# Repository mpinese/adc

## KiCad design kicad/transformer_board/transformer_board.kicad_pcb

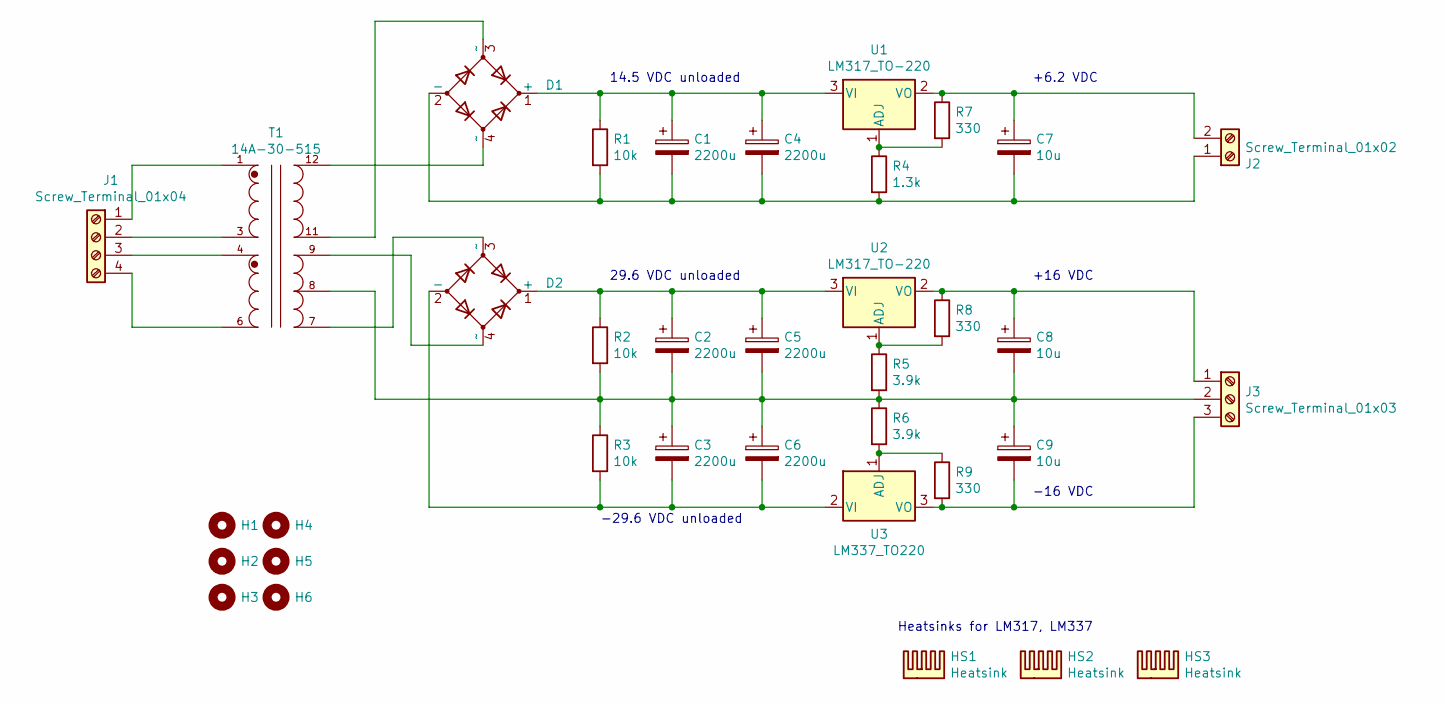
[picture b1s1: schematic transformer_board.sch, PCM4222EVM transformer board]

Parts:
C1, C4: 2200u; CP_Radial_D10.0mm_P5.00mm; DigiKey 565-3869-ND
C2, C3, C5, C6: 2200u; CP_Radial_D12.5mm_P5.00mm; DigiKey 565-3923-ND
C7, C8, C9: 10u; CP_Radial_D5.0mm_P2.00mm; DigiKey 732-9501-1-ND
D1, D2: D_Bridge_+-AA; Diode_Bridge_DIP-4_W7.62mm_P5.08mm; DigiKey DF02MDI-ND
H1, H2, H3, H4, H5, H6: MountingHole; MountingHole_3.2mm_M3
HS1, HS2, HS3: Heatsink; AAVID_504102B00000G; DigiKey HS104-1-ND
J1: Screw_Terminal_01x04; TerminalBlock_Phoenix_PT-1,5-4-5.0-H_1x04_P5.00mm_Horizontal; DigiKey 277-1579-ND
J2: Screw_Terminal_01x02; TerminalBlock_Phoenix_PT-1,5-2-5.0-H_1x02_P5.00mm_Horizontal; DigiKey 277-1667-ND
J3: Screw_Terminal_01x03; TerminalBlock_Phoenix_PT-1,5-3-5.0-H_1x03_P5.00mm_Horizontal; DigiKey 277-1578-ND
R1, R2, R3: 10k; R_Axial_DIN0207_L6.3mm_D2.5mm_P7.62mm_Horizontal; DigiKey PPC10.0KYCT-ND
R4: 1.3k; R_Axial_DIN0207_L6.3mm_D2.5mm_P7.62mm_Horizontal; DigiKey PPC1.30KYCT-ND
R5, R6: 3.9k; R_Axial_DIN0207_L6.3mm_D2.5mm_P7.62mm_Horizontal; DigiKey 56-SFR2500003901FR500CT-ND
R7, R9: 330; R_Axial_DIN0207_L6.3mm_D2.5mm_P7.62mm_Horizontal; DigiKey BC4366CT-ND
R8: 330; R_Axial_DIN0207_L6.3mm_D2.5mm_P7.62mm_Horizontal; DigiKey 56-SFR25H0003300FR500CT-ND
T1: 14A-30-515; XFMR_14A-30-515; DigiKey 595-1828-ND
U1, U2: LM317_TO-220; TO-220-3_Horizontal_TabDown; DigiKey 497-19621-ND
U3: LM337_TO220; TO-220-3_Horizontal_TabDown; DigiKey LM337TGOS-ND

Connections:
unnamed: C1.1, C4.1, D1.1 (+), R1.1, U1.3 (VI)
unnamed: C1.2, C4.2, C7.2, D1.2 (-), J2.1, R1.2, R4.2
unnamed: C2.1, C5.1, D2.1 (+), R2.1, U2.3 (VI)
unnamed: C2.2, C3.1, C5.2, C6.1, C8.2, C9.1, J3.2, R2.2, R3.1, R5.2, R6.1, T1.8
unnamed: C3.2, C6.2, D2.2 (-), R3.2, U3.2 (VI)
unnamed: C7.1, J2.2, R7.1, U1.2 (VO)
unnamed: C8.1, J3.1, R8.1, U2.2 (VO)
unnamed: C9.2, J3.3, R9.2, U3.3 (VO)
unnamed: D1.3 (~~), T1.11
unnamed: D1.4 (~~), T1.12
unnamed: D2.3 (~~), T1.7
unnamed: D2.4 (~~), T1.9
unnamed: J1.1, T1.1
unnamed: J1.2, T1.3
unnamed: J1.3, T1.4
unnamed: J1.4, T1.6
unnamed: R4.1, R7.2, U1.1 (ADJ)
unnamed: R5.1, R8.2, U2.1 (ADJ)
unnamed: R6.2, R9.1, U3.1 (ADJ)

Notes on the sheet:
14.5 VDC unloaded
29.6 VDC unloaded
-29.6 VDC unloaded
+16 VDC
-16 VDC
Heatsinks for LM317, LM337
+6.2 VDC

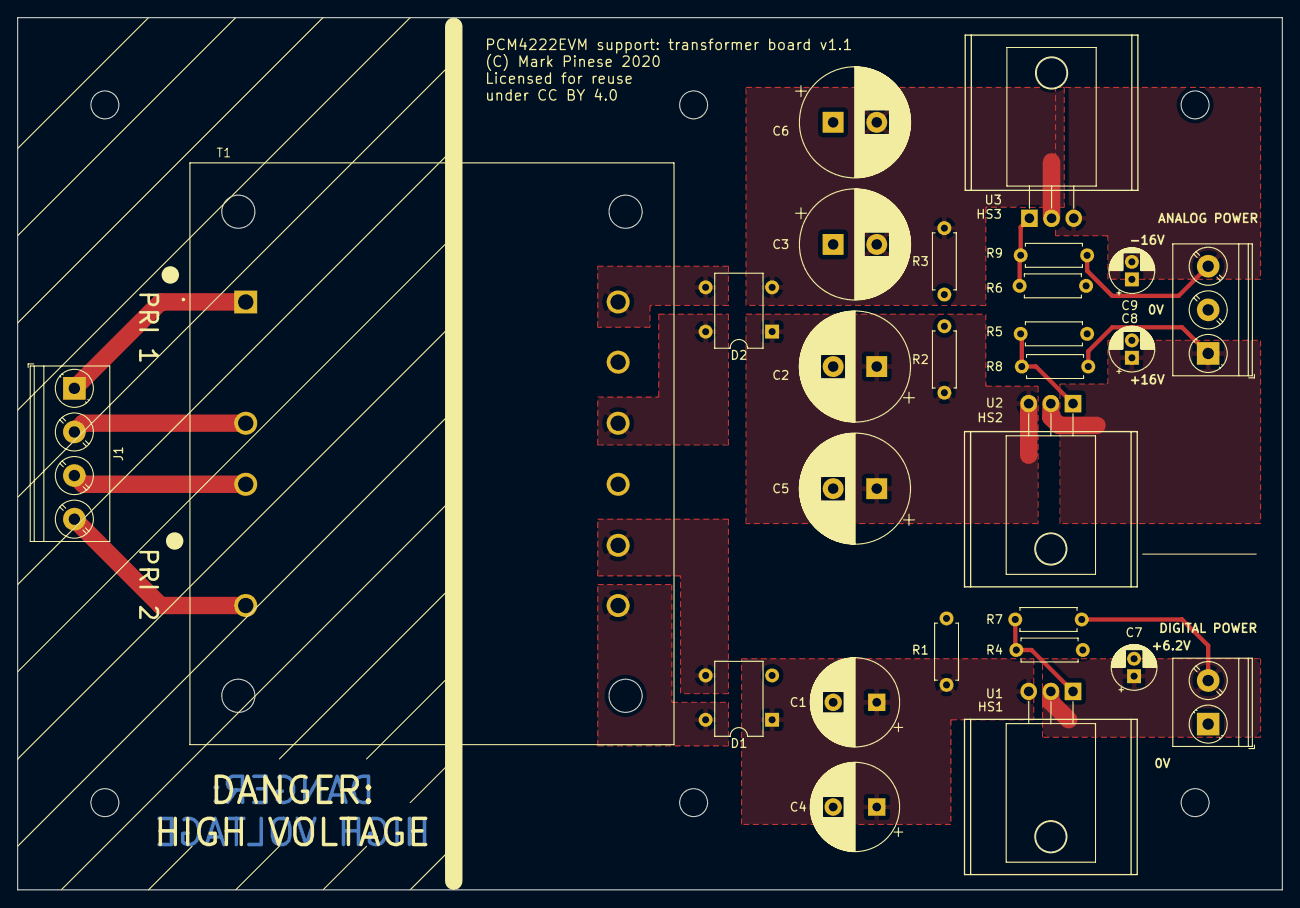
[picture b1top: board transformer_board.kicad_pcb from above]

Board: 2 copper layers, 145.0 x 100.0 mm, 36 parts (0 on the bottom side), 19 nets.

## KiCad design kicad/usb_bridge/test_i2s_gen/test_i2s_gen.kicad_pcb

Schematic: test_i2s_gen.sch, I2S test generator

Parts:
C1: 10u; C_0805_2012Metric; DigiKey 1276-1764-1-ND
C2, C5: 27p; C_0603_1608Metric; DigiKey 311-3929-1-ND
C3: 470n; C_0603_1608Metric; DigiKey 311-1078-1-ND
C4, C6, C7, C8, C9: 100n; C_0603_1608Metric; DigiKey 399-1099-1-ND
H1, H2, H3, H4: MountingHole; MountingHole_2.2mm_M2
J1: Conn_01x02_Male; PinHeader_1x02_P2.54mm_Vertical
J2: Conn_01x04_Male; PinHeader_1x04_P2.54mm_Vertical
R1: 14k; R_0603_1608Metric; DigiKey CR0603-FX-1402ELFCT-ND
R2: 1M; R_0603_1608Metric; DigiKey CR0603-JW-105ELFCT-ND
R3: 21k; R_0603_1608Metric; DigiKey CR0603-FX-2102ELFCT-ND
R4: 4.7k; R_0603_1608Metric; DigiKey CR0603-JW-472ELFCT-ND
S1: 1825910-6; Switch_Tactile_THT_6x6mm; DigiKey 450-1650-ND
U1: SN74AC14DR; SOIC-14_3.9x8.7mm_P1.27mm; DigiKey 296-4300-1-ND
U2: 74AHC86; SOIC-14_3.9x8.7mm_P1.27mm; DigiKey 296-4625-5-ND
U3: 74HC4020; SOIC-16_3.9x9.9mm_P1.27mm; DigiKey MC74HC4020ADR2GOSCT-ND
U4, U5: 74AHC595; SOIC-16_3.9x9.9mm_P1.27mm; DigiKey 1727-5926-1-ND
Y1: Crystal; Crystal_SMD_HC49-SD; DigiKey XC2780CT-ND

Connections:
+3V3: C1.1, C4.1, C6.1, C7.1, C8.1, C9.1, J1.1, R1.2, U1.14, U2.13, U2.14, U3.16, U4.16, U5.16
/BCK: J2.3, U1.8, U3.10, U4.11, U4.12, U5.11, U5.12
/DATA: J2.2, U1.12
/LRCK: J2.4, U1.6
/Reset: U1.1, U1.4, U3.11
/~Reset: U1.2, U4.10, U5.10
GNDD: C1.2, C2.2, C3.2, C4.2, C5.2, C6.2, C7.2, C8.2, C9.2, J1.2, J2.1, R3.1, S1.3, S1.4, U1.7, U2.7, U3.8, U4.8, U4.13, U5.8, U5.13
unnamed: C2.1, R2.2, U1.11, Y1.1
unnamed: C3.1, R1.1, R3.2, S1.1, S1.2, U1.3
unnamed: C5.1, R4.1, Y1.2
unnamed: R2.1, R4.2, U1.9, U1.10
unnamed: U1.5, U3.4
unnamed: U1.13, U2.2, U5.7
unnamed: U2.1, U5.6
unnamed: U2.3, U2.5
unnamed: U2.4, U5.4
unnamed: U2.9, U4.3
unnamed: U2.6, U2.10
unnamed: U2.11, U4.14
unnamed: U2.8, U2.12
unnamed: U4.9, U5.14

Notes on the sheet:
Very basic circuit to test the I2S to USB bridge. Generates left-justified test audio data at 96 kHz 32 bit stereo. This is not strictly I2S format but can be interpreted as such. Simple LFSR to produce the bitstream, so does not test all codes, and would NOT be a good white noise source. 96 kHz st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
Power-on reset circuit. Delay 10 ms.
Vcc: 2.0 to 5.5 V

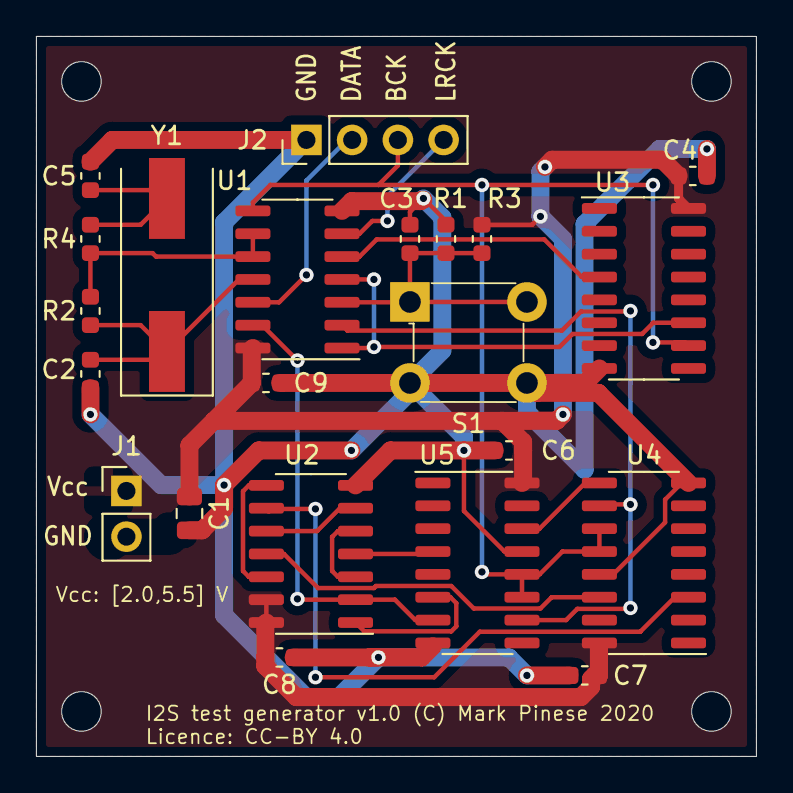
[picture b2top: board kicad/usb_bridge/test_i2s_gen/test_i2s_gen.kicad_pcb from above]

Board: 2 copper layers, 40.0 x 40.0 mm, 26 parts (0 on the bottom side), 21 nets.

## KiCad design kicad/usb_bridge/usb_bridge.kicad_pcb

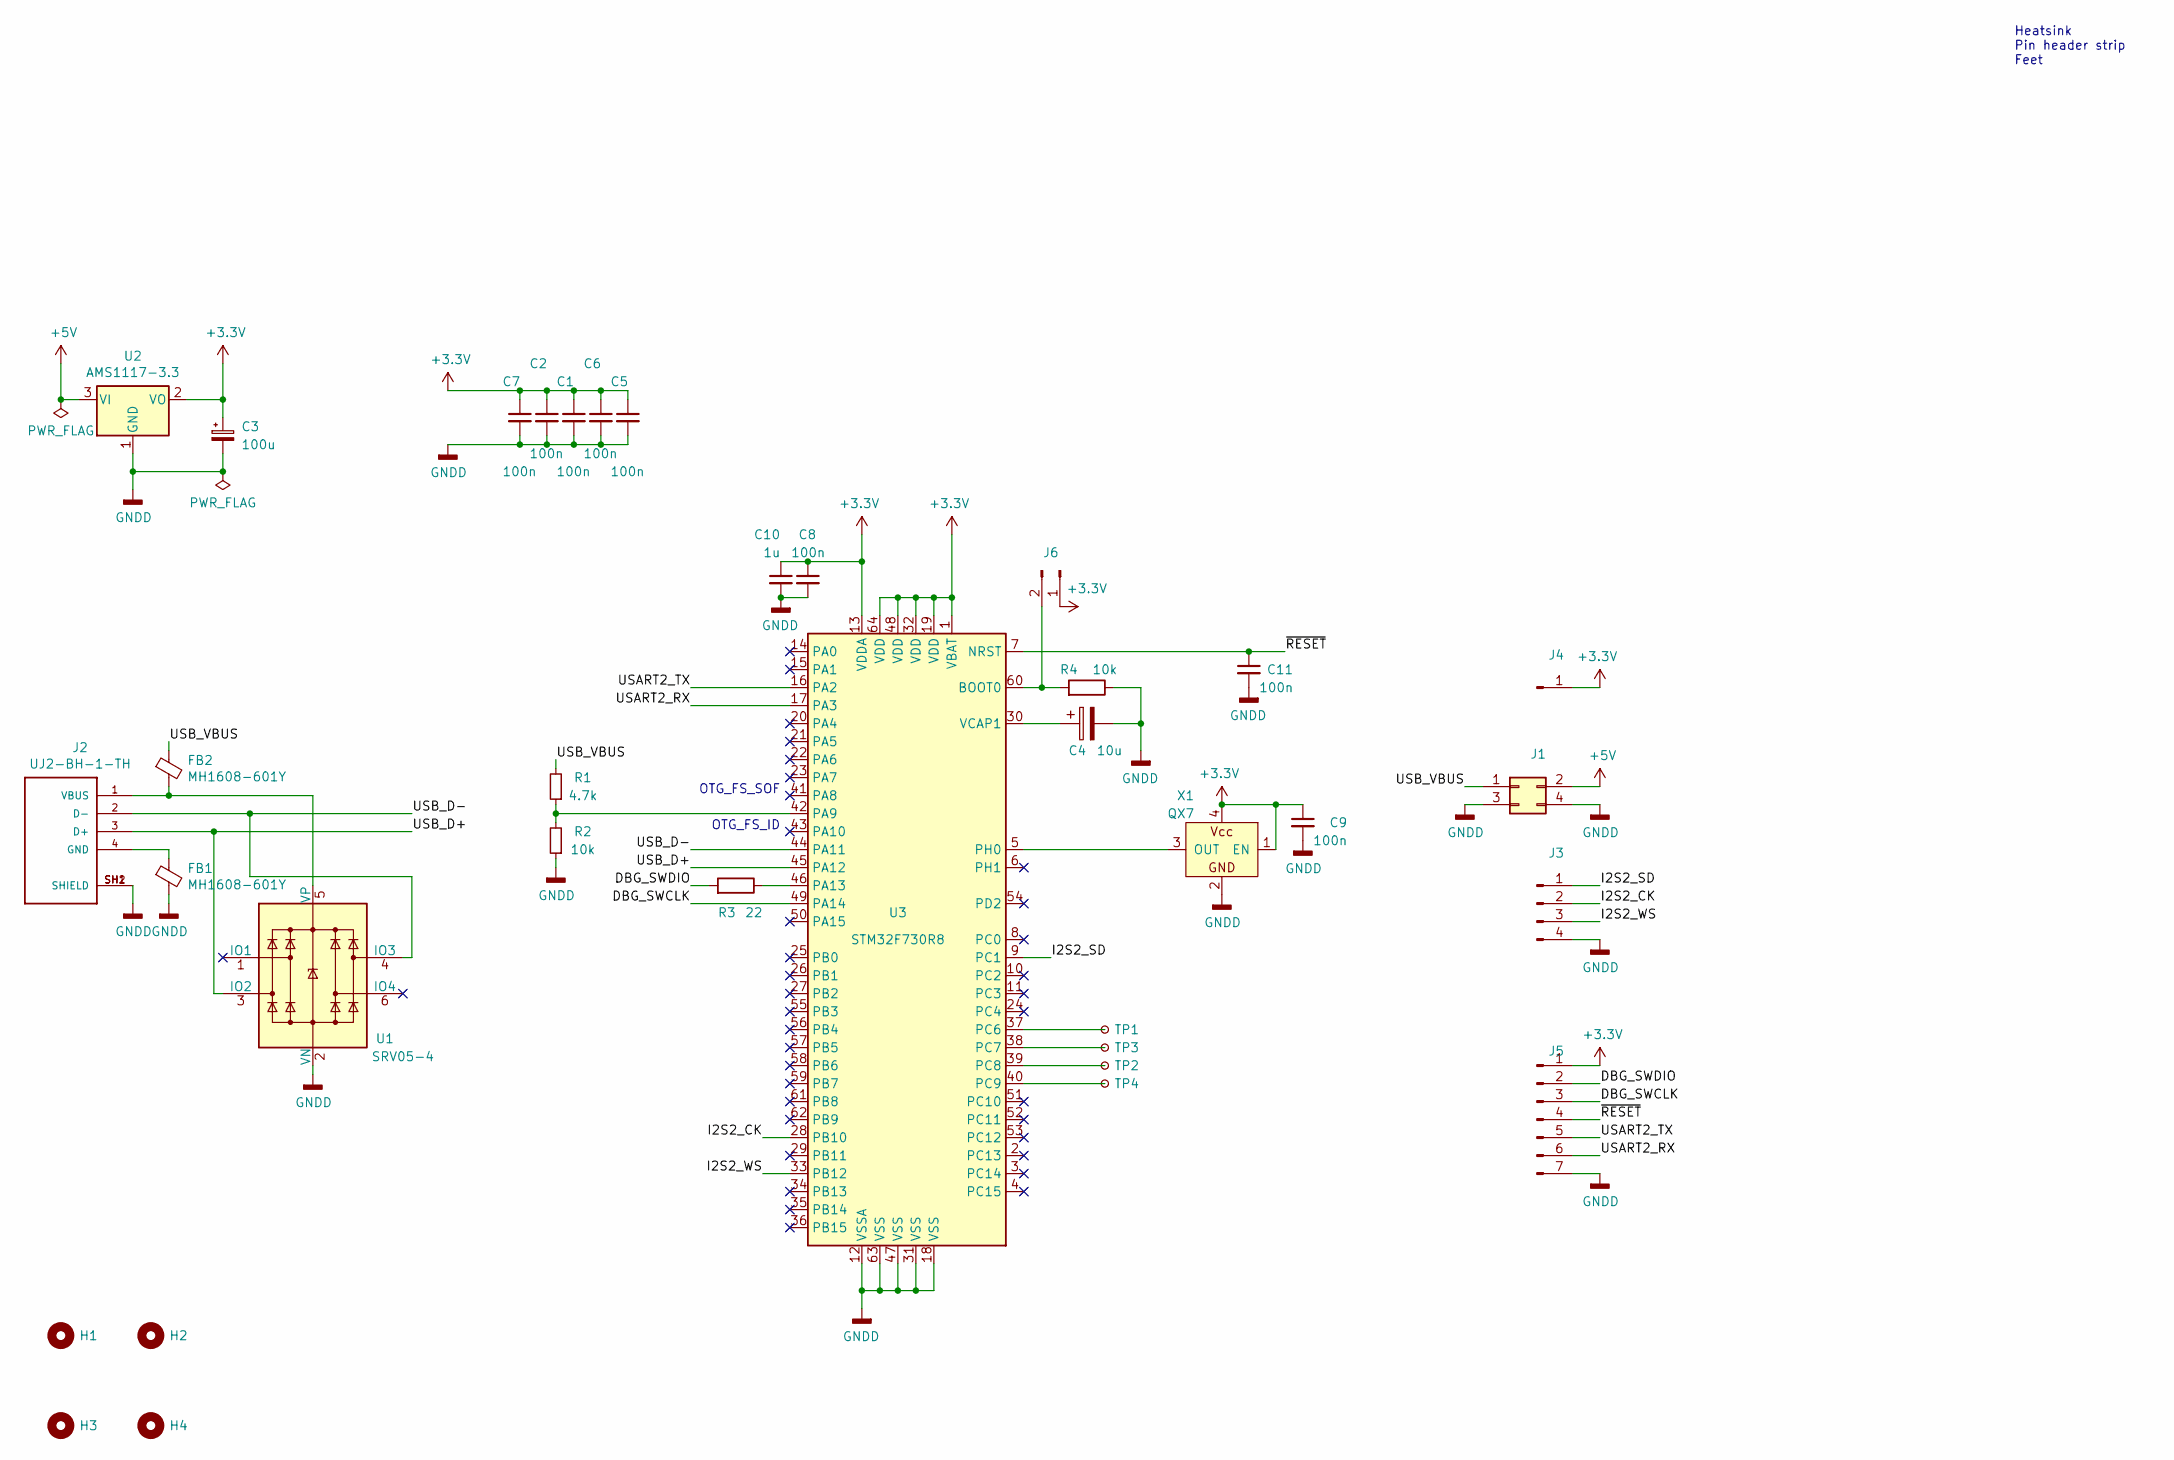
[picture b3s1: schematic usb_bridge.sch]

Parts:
C1, C2, C5, C6, C7, C8, C9, C11: 100n; C_0402_1005Metric; LCSC C1525
C3: 100u; CP_EIA-3528-21_Kemet-B; LCSC C16133
C4: 10u; CP_EIA-2012-15_AVX-P_Pad1.30x1.05mm_HandSolder; DigiKey 718-2064-1-ND
C10: 1u; C_0402_1005Metric; LCSC C52923
FB1, FB2: MH1608-601Y; L_0603_1608Metric; DigiKey MH1608-601YCT-ND
H1, H2, H3, H4: MountingHole; MountingHole_3.2mm_M3
J1: Conn_01x02_Male; PinHeader_2x02_P2.54mm_Vertical
J2: UJ2-BH-1-TH; CUI_UJ2-BH-1-TH; DigiKey 102-3999-ND
J3: Conn_01x04_Male; PinHeader_1x04_P2.54mm_Vertical
J4: Conn_01x01_Male; PinHeader_1x01_P2.54mm_Vertical
J5: Conn_01x07_Male; PinHeader_1x07_P2.54mm_Vertical
J6: Conn_01x02_Male; PinHeader_1x02_P2.54mm_Vertical
R1: 4.7k; R_0402_1005Metric; LCSC C25900
R2, R4: 10k; R_0402_1005Metric; LCSC C25744
R3: 22; R_0402_1005Metric; LCSC C25092
TP1, TP2, TP3, TP4: TestPoint_Small; TestPoint_Pad_D1.0mm
U1: SRV05-4; SOT-23-6; LCSC C85364
U2: AMS1117-3.3; SOT-223-3_TabPin2; LCSC C6186
U3: STM32F730R8; LQFP-64_10x10mm_P0.5mm; DigiKey 497-18103-ND
X1: QX7; QTX333

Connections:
+3V3: C1.1, C2.1, C3.1, C5.1, C6.1, C7.1, C8.1, C9.1, C10.1, J4.1, J5.1, J6.1, U2.2 (VO), U3.1 (VBAT), U3.13 (VDDA), U3.19 (VDD), U3.32 (VDD), U3.48 (VDD), U3.64 (VDD), X1.1 (EN), X1.4
+5V: J1.2, U2.3 (VI)
/DBG_SWCLK: J5.3, U3.49 (PA14)
/DBG_SWDIO: J5.2, R3.2
/I2S2_CK: J3.2, U3.28 (PB10)
/I2S2_SD: J3.1, U3.9 (PC1)
/I2S2_WS: J3.3, U3.33 (PB12)
/USART2_RX: J5.6, U3.17 (PA3)
/USART2_TX: J5.5, U3.16 (PA2)
/USB_D+: J2.3 (D+), U1.3 (IO2), U3.45 (PA12)
/USB_D-: J2.2 (D-), U1.4 (IO3), U3.44 (PA11)
/USB_VBUS: FB2.1, J1.1, R1.2
/~RESET: C11.1, J5.4, U3.7 (NRST)
GNDD: C1.2, C2.2, C3.2, C4.2, C5.2, C6.2, C7.2, C8.2, C9.2, C10.2, C11.2, FB1.2, J1.3, J1.4, J2.SH1 (SHIELD), J2.SH2 (SHIELD), J3.4, J5.7, R2.1, R4.1, U1.2 (VN), U2.1 (GND), U3.12 (VSSA), U3.18 (VSS), U3.31 (VSS), U3.47 (VSS), U3.63 (VSS), X1.2
unnamed: C4.1, U3.30 (VCAP1)
unnamed: FB1.1, J2.4 (GND)
unnamed: FB2.2, J2.1 (VBUS), U1.5 (VP)
unnamed: J6.2, R4.2, U3.60 (BOOT0)
unnamed: R1.1, R2.2, U3.42 (PA9)
unnamed: R3.1, U3.46 (PA13)
unnamed: TP1.1, U3.37 (PC6)
unnamed: TP2.1, U3.39 (PC8)
unnamed: TP3.1, U3.38 (PC7)
unnamed: TP4.1, U3.40 (PC9)
unnamed: U3.5 (PH0), X1.3 (OUT)

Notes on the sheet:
Heatsink Pin header strip Feet
OTG_FS_SOF
OTG_FS_ID

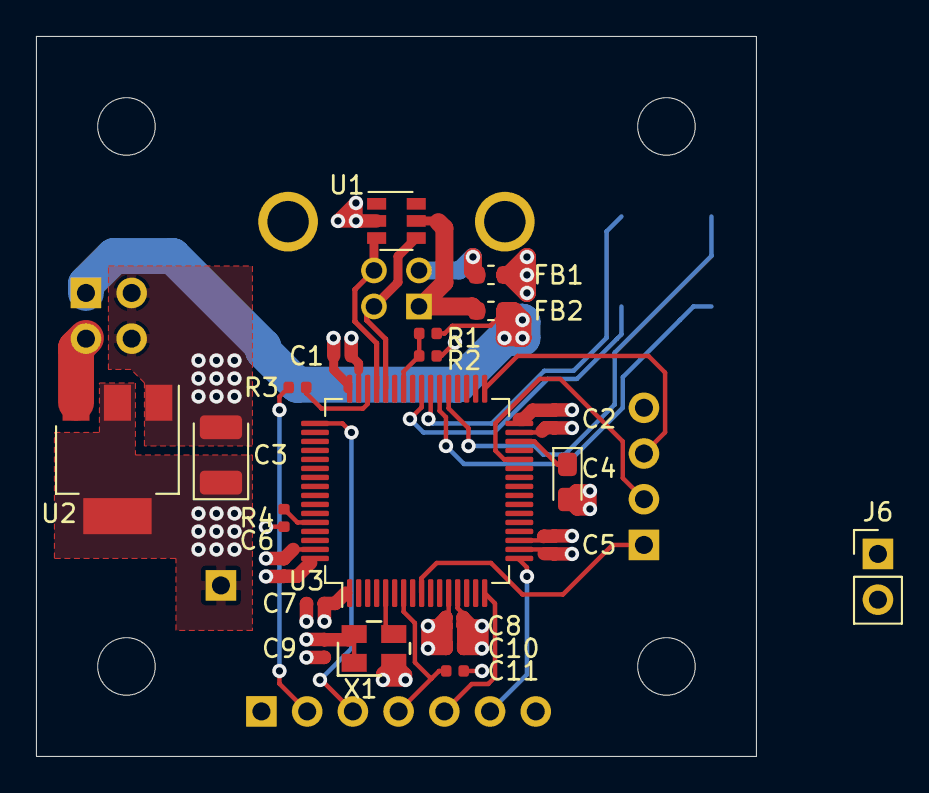
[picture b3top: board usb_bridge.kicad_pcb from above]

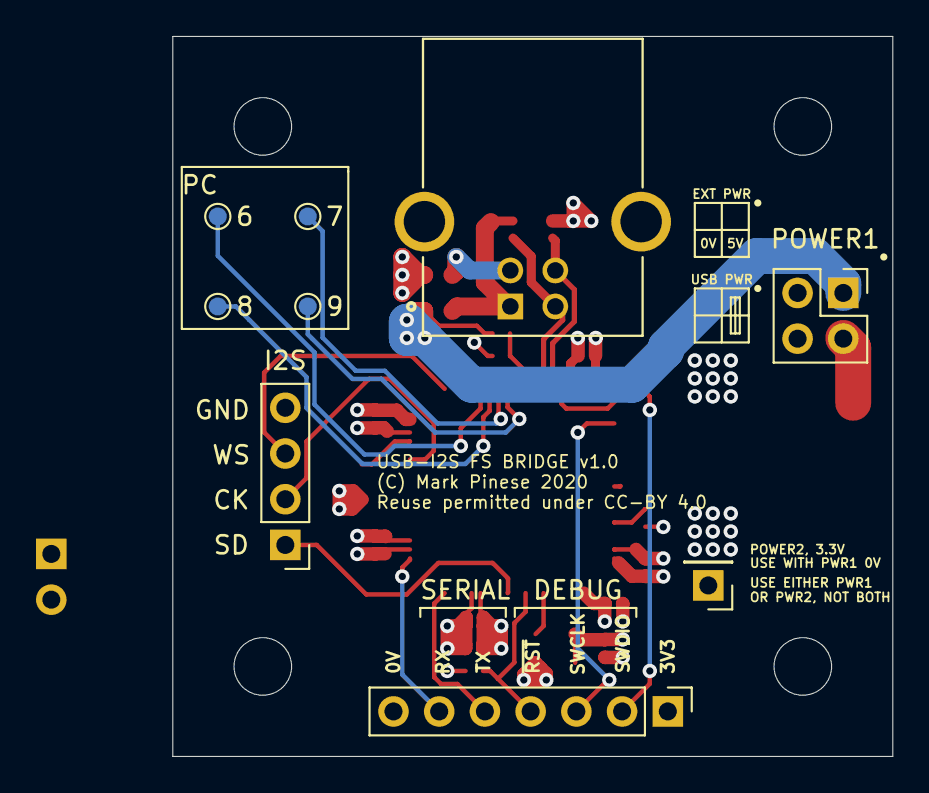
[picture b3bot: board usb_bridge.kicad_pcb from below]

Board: 4 copper layers, 40.0 x 40.0 mm, 35 parts (9 on the bottom side), 25 nets.

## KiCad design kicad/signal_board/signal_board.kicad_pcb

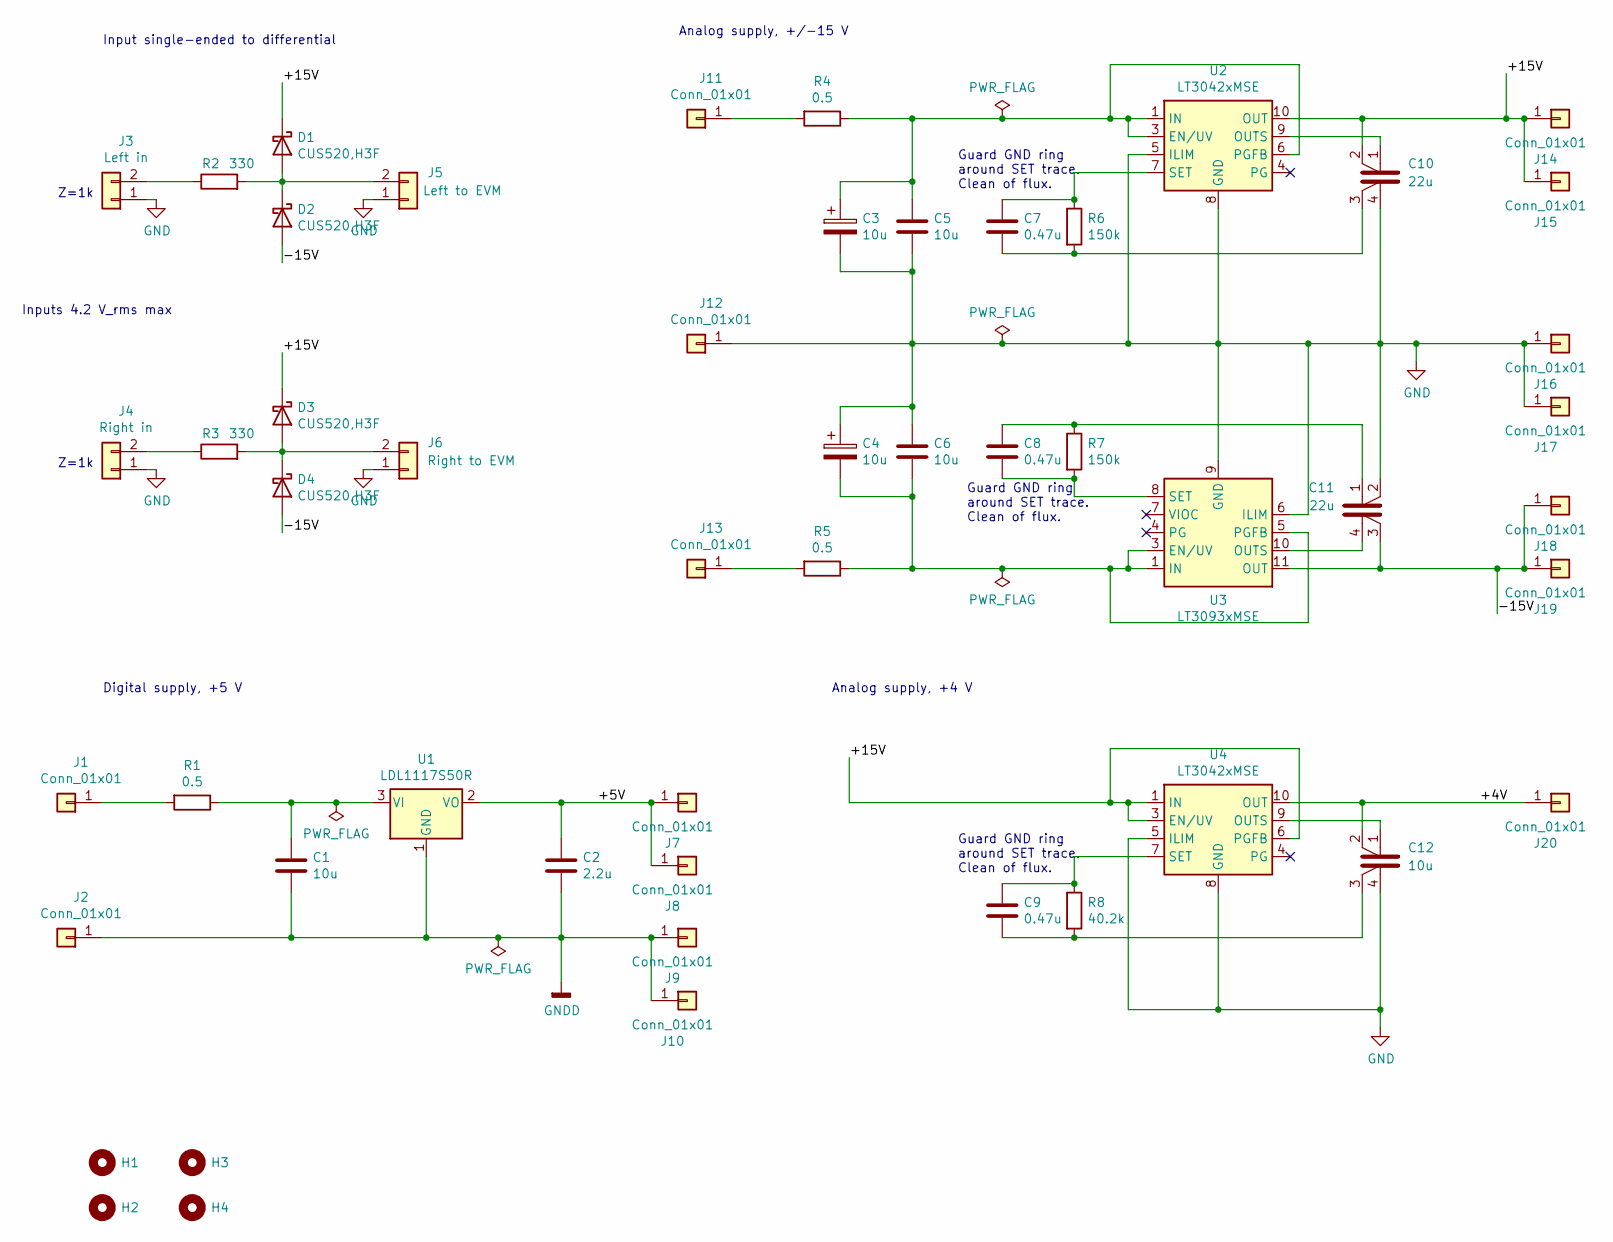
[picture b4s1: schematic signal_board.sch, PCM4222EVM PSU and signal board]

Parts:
C1: 10u; C_1206_3216Metric; DigiKey 1276-6767-1-ND
C2: 2.2u; C_0805_2012Metric; DigiKey 1276-6655-1-ND
C3, C4: 10u; CP_EIA-3528-21_Kemet-B; DigiKey 718-1926-1-ND
C5, C6: 10u; C_1206_3216Metric; LCSC C13585
C7, C8, C9: 0.47u; C_0805_2012Metric; LCSC C13967
C10, C11: 22u; C_1210_3225Metric_Split; DigiKey 1276-3392-1-ND
C12: 10u; C_1206_3216Metric_Split; DigiKey 1276-3107-1-ND
D1, D2, D3, D4: CUS520,H3F; D_SOD-323; DigiKey CUS520H3FCT-ND
H1, H2, H3, H4: MountingHole; MountingHole_3.2mm_M3
J1, J2, J7, J8, J9, J10, J11, J12, J13, J14, J15, J16, J17, J18, J19, J20: Conn_01x01; SolderWirePad_1x01_Drill1mm
J3: Left in; PinHeader_1x02_P2.54mm_Vertical
J4: Right in; PinHeader_1x02_P2.54mm_Vertical
J5: Left to EVM; PinHeader_1x02_P2.54mm_Vertical
J6: Right to EVM; PinHeader_1x02_P2.54mm_Vertical
R1, R4, R5: 0.5; R_0805_2012Metric; DigiKey RL12S.50FCT-ND
R2, R3: 330; R_0603_1608Metric; DigiKey RG16P330BCT-ND
R6, R7: 150k; R_0603_1608Metric; DigiKey RG16P150KBCT-ND
R8: 40.2k; R_0603_1608Metric; DigiKey RG16P40.2KBCT-ND
U1: LDL1117S50R; SOT-223-3_TabPin2; DigiKey 497-17240-1-ND
U2, U4: LT3042xMSE; MSOP-10-1EP_3x3mm_P0.5mm_EP1.68x1.88mm_ThermalVias; DigiKey LT3042EMSE#PBF-ND
U3: LT3093xMSE; MSOP-12-1EP_3x4mm_P0.65mm_EP1.65x2.85mm_ThermalVias; DigiKey LT3093EMSE#PBF-ND

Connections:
/+4V: C12.2, J20.1, U4.10 (OUT)
/+5V: C2.1, J7.1, J8.1, U1.2 (VO)
/+15V: C10.2, D1.1 (K), D3.1 (K), J14.1, J15.1, U2.10 (OUT), U4.1 (IN), U4.2 (IN), U4.3 (EN/UV), U4.6 (PGFB)
/-15V: C11.3, D2.2 (A), D4.2 (A), J18.1, J19.1, U3.11 (OUT), U3.12 (OUT)
GND: C3.2, C4.1, C5.2, C6.1, C10.4, C11.2, C12.4, J3.1, J4.1, J5.1, J6.1, J12.1, J16.1, J17.1, U2.5 (ILIM), U2.8 (GND), U2.11 (GND), U3.6 (ILIM), U3.9 (GND), U4.5 (ILIM), U4.8 (GND), U4.11 (GND)
GNDD: C1.2, C2.2, J2.1, J9.1, J10.1, U1.1 (GND)
unnamed: C1.1, R1.1, U1.3 (VI)
unnamed: C3.1, C5.1, R4.1, U2.1 (IN), U2.2 (IN), U2.3 (EN/UV), U2.6 (PGFB)
unnamed: C4.2, C6.2, R5.1, U3.1 (IN), U3.2 (IN), U3.3 (EN/UV), U3.5 (PGFB), U3.13 (IN)
unnamed: C7.1, R6.1, U2.7 (SET)
unnamed: C8.2, R7.2, U3.8 (SET)
unnamed: C9.1, R8.1, U4.7 (SET)
unnamed: C10.1, U2.9 (OUTS)
unnamed: C7.2, C10.3, R6.2
unnamed: C8.1, C11.1, R7.1
unnamed: C11.4, U3.10 (OUTS)
unnamed: C12.1, U4.9 (OUTS)
unnamed: C9.2, C12.3, R8.2
unnamed: D1.2 (A), D2.1 (K), J5.2, R2.2
unnamed: D3.2 (A), D4.1 (K), J6.2, R3.2
unnamed: J1.1, R1.2
unnamed: J3.2, R2.1
unnamed: J4.2, R3.1
unnamed: J11.1, R4.2
unnamed: J13.1, R5.2

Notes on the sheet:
Guard GND ring around SET trace. Clean of flux.
Z=1k
Input single-ended to differential
Digital supply, +5 V
Analog supply, +/-15 V
Analog supply, +4 V
Inputs 4.2 V_rms max

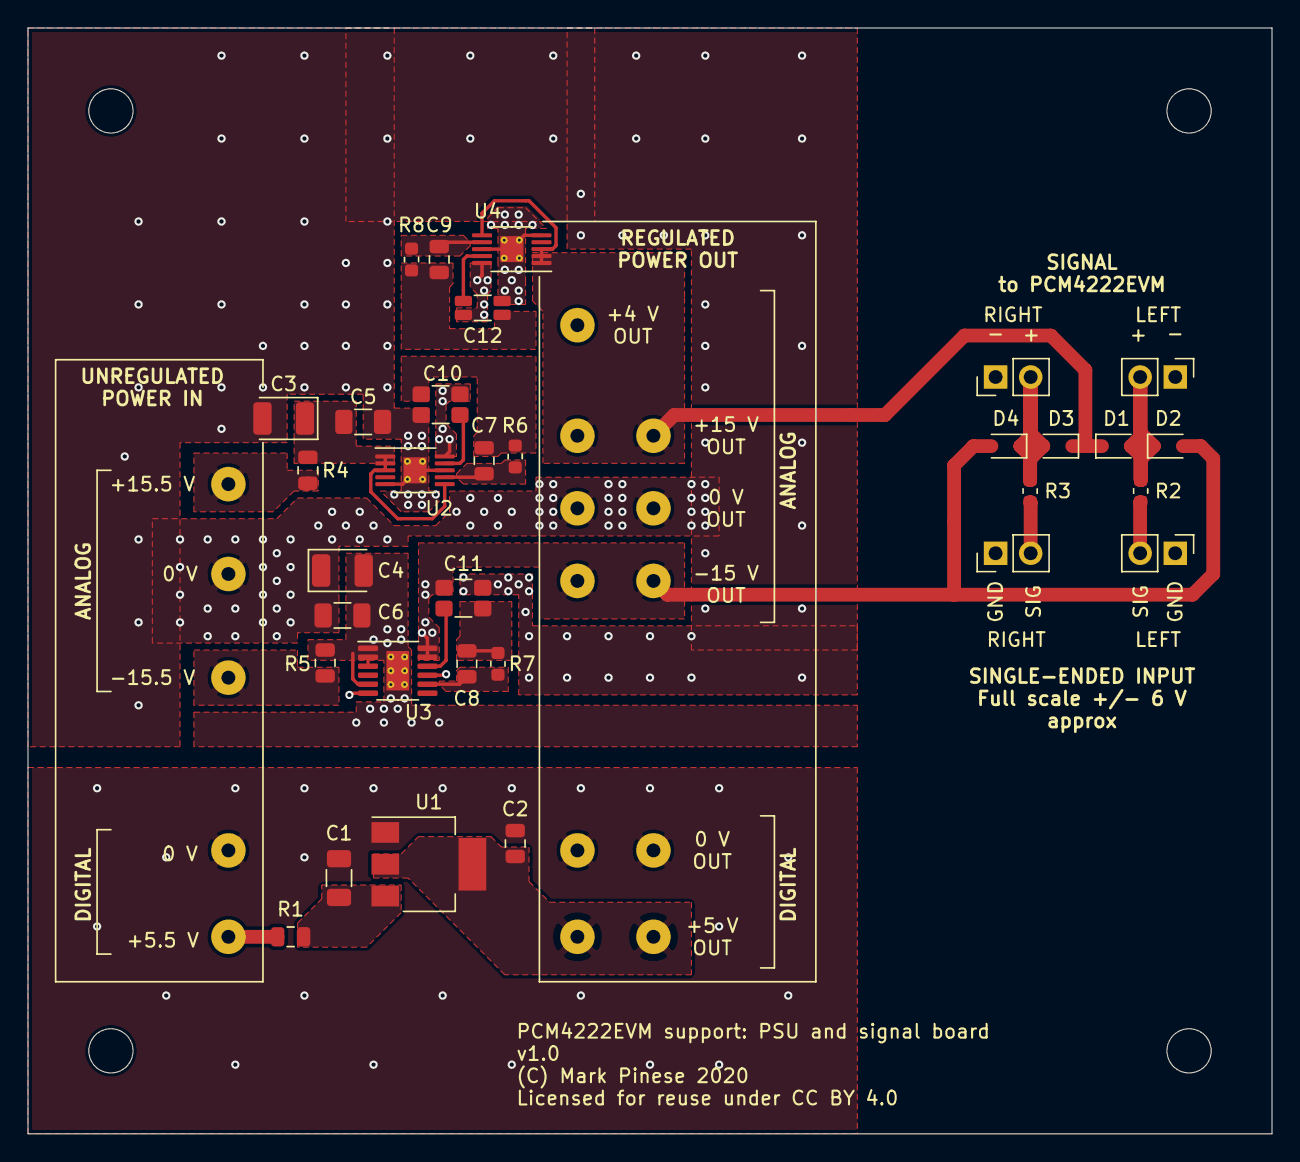
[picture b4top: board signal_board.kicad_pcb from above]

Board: 2 copper layers, 90.0 x 80.0 mm, 52 parts (0 on the bottom side), 25 nets.

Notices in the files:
ADC.kicad_pcb:
Design licensed under Creative Commons BY-SA v4.0
http://creativecommons.org/licenses/by-sa/4.0
kicad/signal_board/signal_board.kicad_pcb:
Made available for reuse under the CC BY 4.0 Licence
Licensed for reuse under CC BY 4.0
kicad/transformer_board/transformer_board.kicad_pcb:
under CC BY 4.0
kicad/usb_bridge/test_i2s_gen/test_i2s_gen.kicad_pcb:
(C) 2020
Licenced for reuse under CC-BY 4.0
Licence: CC-BY 4.0
kicad/usb_bridge/usb_bridge.kicad_pcb:
Reuse permitted under CC-BY 4.0
